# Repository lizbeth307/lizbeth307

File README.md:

<div align="center">
  
</div>

<div align="center">

</div>

<div align="center">

</div>

<div align="center">
  
</div>

<br>

<div align="center">

</div>

<br>

<div align="center">
  
</div>

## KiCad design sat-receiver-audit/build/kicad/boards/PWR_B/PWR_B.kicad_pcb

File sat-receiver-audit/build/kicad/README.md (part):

# KiCad SR-RX-v2.1 — відтворення схем і перевірок

> **Стан 20.10.2026:** ПЗ керування Pico/IMU та labd/labctl реалізоване й пройшло хостові тести; див. [актуальний запуск](../../software/README.md). Фізичне встановлення/приймання не виконано. Старі фрази про відсутню прошивку нижче описують етап 19.10.

> **Ревізія 23.10.2026:** CI workflow «SR-RX verification» (job `cad`) запускає `tools/run_checks.py --export` в офіційному образі `kicad/kicad:10.0.7` і порівнює результат із закоміченим. Допускаються лише рядки з датами експорту, абсолютними шляхами, build string KiCad, `"design_file"` і змінені рядки `"sha256"`/`"netlist_sha256"` у JSON-звітах (будь-який 64-символьний hash, не лише netlist); інша різниця дає помилку й артефакт `cad-regenerated` із патчем. `sr-rx-v2.pdf` побайтово не порівнюється: його фіксує лише `verification/pdf-export.json`, де змінений рядок `"sha256"` теж допускається. У цій ревізії R512 отримав `R_1210_3225Metric` (0.5 W); дубльовані підтяжки R102/R503/R507/R511 вилучено з графів під час злиття з гілкою `ccr-1537979d-cj7q9t` (а не позначено DNP): 750 елементів / 2181 підключений контакт / 466 мереж, 14 електричних сторінок. Зведення — [HANDOFF](../../HANDOFF.md#ревізія-23102026-claude-перевірка-виправлення-ci-план).

> **Ревізія генератора 24.10.2026:** E1 знову вміщується на одну сторінку; разом із п'ятою сторінкою E2 (блокувальні пари ±30 V, рішення власника v2.1) комплект має 14 електричних сторінок і зміст (PDF — 15 сторінок). Якщо остання сторінка аркуша була б майже порожньою (блоки займають менше 20 % площі), генератор переносить примітки ширшими рядками, наскільки дозволяє ширина креслення групи, і лишає найвужчий варіант, що заощаджує сторінку (для E1 — до 180 символів замість 110; примітка вужчої групи лишається вужчою: E1-02 — 121, E1-06 — 110). Рядок, де мітці знадобилося резервне (fallback) місце або дроти перетнули іншу мережу, розкладається ще раз із вільним кроком сітки біля кожного контакту шини між двома коробками, що стоять одна навпроти одної; цей варіант лишається, лише якщо в ньому менше fallback-міток або, за тієї самої їх кількості, щонайбільше вдвічі менше перетинів. Так розкладено HDMI J520–U520, PCIe J530–U530 та I²C/RESET між U302 і U303 (без перетинів) і SPI U309–U314 (частина перетинів лишилася): fallback-міток 0 замість 4; перетинів дротів без з'єднання на весь комплект — 45 (`drawing.wire_crossings`). Правий край вмісту разом із прив'язкою рядків до сітки лишається щонайменше на крок сітки (2.54 мм) від внутрішньої рамки. `generation-manifest.json` записує для кожної сторінки заповнення (`fill`), межу ширини приміток аркуша (`note_wrap_cap`), фактичну ширину рядків кожної примітки в символах (`note_wrap_chars`), fallback-мітки та перетини (`wire_crossings`), а також `sparse_last_pages`; `run_checks.py` відмовляє, якщо лишилася майже порожня остання сторінка або fallback-мітка. Згенеровані файли перегенеровує CI (`cad-regenerated`); оскільки з `netlist.xml` зник аркуш `/E1_02/`, змінився і вхід DC_CORE; DC_CORE перезаморожено 24.10.2026 (`refreeze_pcb`, вхід `14a5d398…`). Поле `electrical_sheets` у `verification/validation.json` тепер рахує лише аркуші з елементами (`schematic_sheets` — усі, `index_sheets` — кореневий зміст).

Поточна редакція від 19.10.2026 генерується локальними Python-інструментами з `design/E1.json`–`E5.json`. У вихідному коміті Claude `4653188` (у переписаній історії `ccr-1537979d-cj7q9t` — `4ffcc1d`) усі п'ять електричних E1–E5 були порожніми, а пізніші часткові аркуші Claude `e95fec4` (там — `9063cfa`) влито merge-комітом без зміни дерева; тому історичний опис «побудовано через KiCad MCP» нижче не підтверджує походження поточних схем.

## Склад актуального комплекту

- `sr-rx-v2.kicad_pro` / `sr-rx-v2.kicad_sch` — проєкт і кореневий зміст. E1–E5 поділяються генератором на додаткові електричні сторінки; їхній точний перелік — `generation-manifest.json`.

Креслення (з 23.10.2026). Кожна функціональна група — окремий блок на одній сторінці: заголовок один раз, примітки OPEN/TBD поруч із її частинами. У рядку сигнал іде зліва направо: мікросхеми, модулі, транзистори й послідовні елементи стоять на сигнальній лінії, підтягувальні резистори й контрольні точки — над нею, шунтові елементи (розв'язувальні конденсатори, дільники, TVS, демпфери) — під нею, земля — символ GND унизу. Контакти однієї мережі в рядку з'єднано ортогональними дротами з точками на T-з'єднаннях; контакт, до якого дріт довелося б вести довгим обхідним шляхом, отримує мітку. Кожне дерево дротів має рівно одну глобальну мітку з канонічною назвою мережі (рамка-стрілка — мережа виходить за межі групи, пряма рамка — мережа лише цієї групи), бо локальну мітку KiCad перейменував би на «/<аркуш>/<назва>» і змінив би netlist. Транзистори й діоди мають стандартні графічні символи KiCad (Device: Q_NMOS/Q_PMOS, D, D_Zener, D_Schottky, LED) з незмінною нумерацією контактів. Генератор сам відновлює зв'язність кожної сторінки з геометрії (кінці дротів, контакти, мітки, GND) і не записує сторінку, де вона розходиться з графом.
- `sr_rx_v2_completed.kicad_sym` — бібліотека з поточних графів; початкові `sr_rx_v2_pwr.kicad_sym` / `sr_rx_v2_sig.kicad_sym` збережені. Бібліотечні шляхи відносні.
- `sr-rx-v2.pdf` та `svg/` — результати CLI-експорту після успішних перевірок; не результат вимірювання заліза.
- `../../verification/erc.json` — повний сирий ERC; `validation.json` — незалежне зіставлення netlist із графами; інваріанти й розрахунок DC-detector — окремі відтворювані перевірки.

Розширені позначення нових детекторів E4 використовують R/C4400–4499; старі діапазони 100–599 збережені для початкових вузлів. Бібліотека відображає фізичні контакти IC і явно названі функціональні інтерфейси готових модулів; останні не є вигаданою нумерацією pad невідомої плати.

## Команди

З каталогу `sat-receiver-audit`, у Python 3 з установленим KiCad 10 CLI. Для офлайн-HTML додатково потрібні Pandoc і Python-залежності з `tools/requirements.txt` (`python3 -m pip install -r tools/requirements.txt`):

```bash
python3 tools/run_checks.py --export
python3 tools/build_bundle.py
```

Другу команду виконувати після успішного завершення першої. Якщо CLI не в PATH:

```bash
python3 tools/run_checks.py --kicad-cli /повний/шлях/до/kicad-cli --export
```

`run_checks.py` послідовно генерує схеми, експортує XML netlist, записує ERC, порівнює мережі, перевіряє незалежні електричні інваріанти та DC-detector, формує документи й за `--export` PDF/SVG. `build_bundle.py` пакує офлайн-HTML із вихідним архівом. Пакування не замінює перевірки. Запуск у CI після W2 GR-3 (sr-rx-verify, 07.11.2026; роз'єми джгутів — позиції графа) завершено: 839 елементів, 2555 контактів, 486 мереж, 163 явних NC, 17 сторінок разом зі змістом (16 електричних); ERC 0 помилок і 0 попереджень, netlist PASS (CI/model, не апаратний результат); повторний запуск дає байт-у-байт ті самі файли. Після будь-якої зміни графів ці результати потрібно отримати повторно.

PDF експортується без property popups та hierarchical links: у використаному KiCad 10.0.7 початковий експорт з анотаціями повертав exit 0, але неповний PDF. Генератор додатково перевіряє завершення `%%EOF`. Поточний PDF має 15 сторінок A2 (14 електричних і зміст; 24.10.2026 E1_02 злито в E1 і додано E2_05); його прив'язує до схем `verification/pdf-export.json`. Перевірку PDF-парсерами й візуальний перегляд виконано 23.10.2026 для PDF гілки `ccr-1537979d-cj7q9t` до злиття ([звіт](../../verification/pdf-visual-review.md)); на перегенерований після злиття PDF їхній результат не переноситься, доки сторінки не переглянуто знову.

## Межа готовності

**Апаратний випуск BLOCKED.** ERC та збіг netlist не перевіряють фізичну ревізію модулів, нагрівання, струм запуску, USB/PCIe SI, RF, калібровку батарейного ADC або механіку. [OPEN_ITEMS](../../OPEN_ITEMS.md) і [v2.1](../12-revision-v2.1.md) мають бути прочитані до монтажу. ISDT/raw-balance та щомісячне балансування заблоковані до E1-02; J102 DNP/service-only.

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
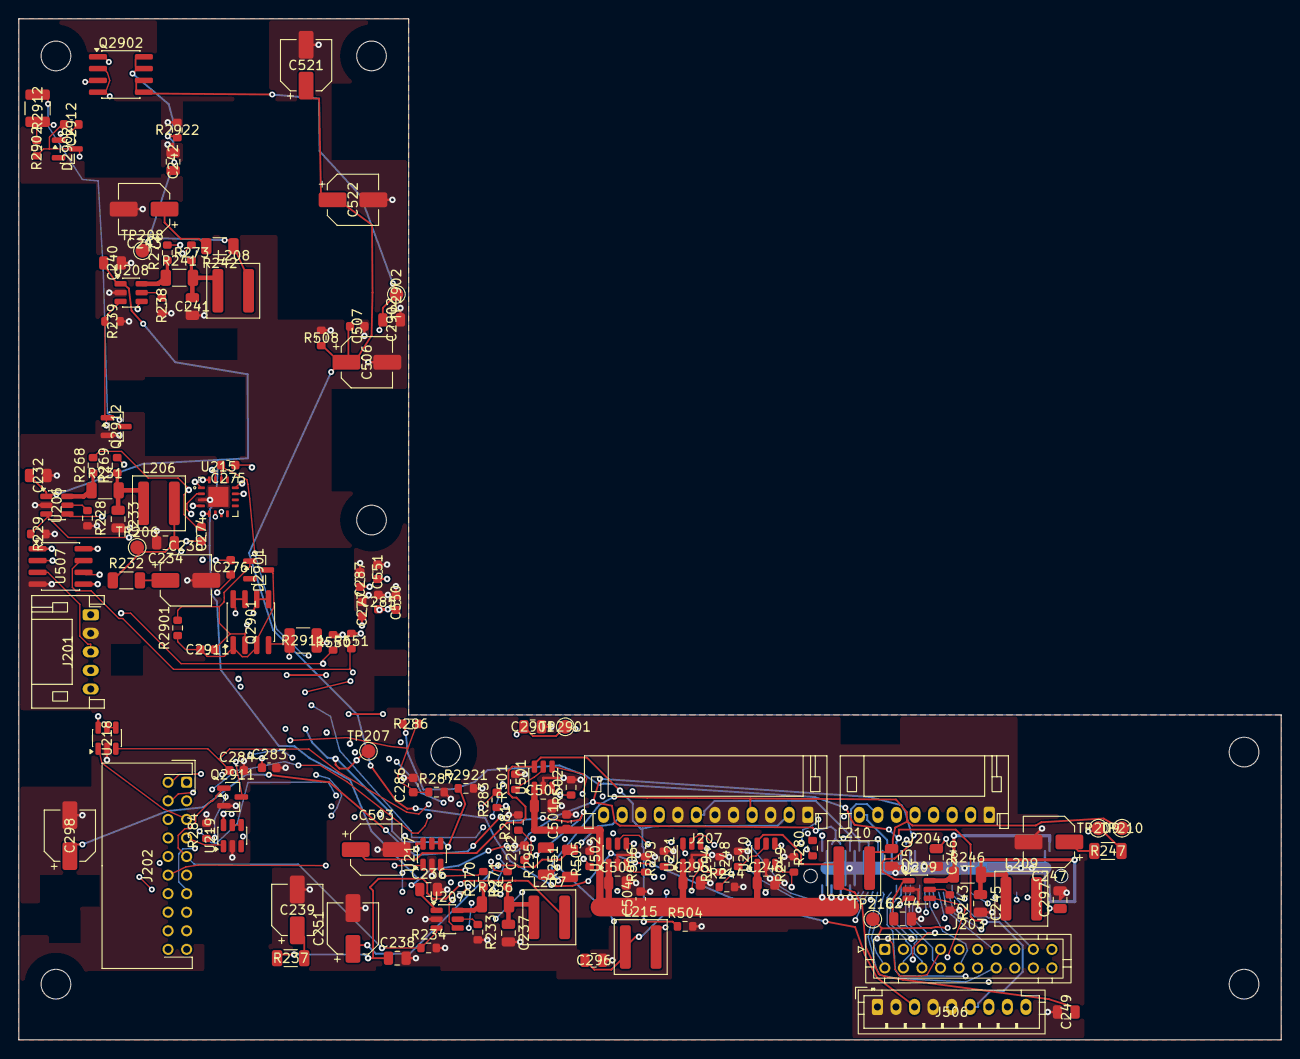
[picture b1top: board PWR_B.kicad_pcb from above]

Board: 6 copper layers, 136.0 x 110.0 mm, 144 parts (1 on the bottom side), 106 nets.

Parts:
C232, C233, C234, C236, C237, C238, C240, C241, C242, C244, C245, C246, C248, C249, C250, C295, C296, C297, C2901, C2902: 1uF 50V X7R C2012X7R1H105K125AB; C_0805_2012Metric
C235, C239, C243, C247, C251, C298, C506, C521, C522: 47uF 10V 16SVPG47M; CP_Elec_5x4.5
C274, C275, C276, C277, C283, C285, C287, C2911, C2912: 100nF 50V X7R C1608X7R1H104K080AA; C_0603_1608Metric
C282, C284, C286: 10nF 50V C0G C1608C0G1H103J080AA; C_0603_1608Metric
C501, C504, C507, C550, C551: 100nF X7R 10V; C_0603_1608Metric
C502, C505: 4.7uF X7R 10V; C_0805_2012Metric
C503: 47uF 10V; CP_Elec_5x4.5
D2901, D2902: BZX84C10-7-F; SOT-23
H1, H2, H3, H4, H5, H6, H7: NPTH_3.2mm
J201: X02S0-PWR: JST PH 5, боковий вхід, S02; JST_PH_S5B-PH-K_1x05_P2.00mm_Horizontal
J202: S02-PWR-SIG-1: JST PHD 2×10, боковий вхід, S02; JST_PHD_S20B-PHDSS_2x10_P2.00mm_Horizontal
J203: S02-PWR-SIG-2: JST PHD 2×10, верхній вхід, S02B; JST_PHD_B20B-PHDSS_2x10_P2.00mm_Vertical
J204: X04S1-PWR: JST PH 8, боковий вхід, S04; JST_PH_S8B-PH-K_1x08_P2.00mm_Horizontal
J207: SL2-PWR-PH: JST PH 12, боковий вхід, S20, S21, S2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; JST_PH_S12B-PH-K_1x12_P2.00mm_Horizontal
J209: B2B-PWRB: Samtec LSHM-150 2×50, PWR-B низ, стик 5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; Samtec_LSHM-150-xx.x-x-DV-N_2x50_P0.50mm_Vertical
J506: SL3-PWR-PH: JST PH 9, верхній вхід, S23, S34; JST_PH_B9B-PH-K_1x09_P2.00mm_Vertical
L206, L207, L208, L209, L210, L215: 1uH XAL5030-102MEC; L_Coilcraft_XAL5030-XXX
Q2901, Q2902: DMP6050SSD-13; SOIC-8_3.9x4.9mm_P1.27mm
Q2911, Q2912: 2N7002; SOT-23
R228, R233, R238: 88.7k 1%; R_0603_1608Metric
R229, R234, R239, R244, R249, R294: 100k 1%; R_0603_1608Metric
R231, R236, R241, R246: 0.200R 0.1% 0.25W Kelvin; R_1206_3216Metric
R232, R237, R242, R247, R251, R295: 0.15R 1% 0.25W; R_1206_3216Metric
R243, R293: 162k 1%; R_0603_1608Metric
R248: RILIM TBD (start 56.2k 1%); R_0603_1608Metric
R268, R269, R270, R271, R272, R273: 10.0R 1%; R_0603_1608Metric
R280: 85.6k 0.1%; R_0603_1608Metric
R281, R284, R287: 10.0k 0.1%; R_0603_1608Metric
R283: 90.9k 0.1%; R_0603_1608Metric
R286: 73.2k 0.1%; R_0603_1608Metric
R501: RILIM TBD (start 43.2k 1%); R_0603_1608Metric
R502, R506: 100k; R_0603_1608Metric
R504, R508: 10k; R_0603_1608Metric
R505: 34.8k 1%; R_0603_1608Metric
R550, R551, R2921, R2922: 4.7k 1%; R_0603_1608Metric
R2901, R2902: 220k 1%; R_0603_1608Metric
R2911, R2912: 4.7k 1% ≥0.25W; R_1210_3225Metric
TP206: BIAS_CH1; TestPoint_Pad_D1.5mm
TP207: BIAS_CH2; TestPoint_Pad_D1.5mm
TP208: BIAS_CH3; TestPoint_Pad_D1.5mm
TP209: BIAS_CH4; TestPoint_Pad_D1.5mm
TP210: VBUS_RTLB; TestPoint_Pad_D1.5mm
TP216: BIAS_SB_LNA; TestPoint_Pad_D1.5mm
TP2901: BIAS_CH2_PORT; TestPoint_Pad_D1.5mm
TP2902: BIAS_CH3_PORT; TestPoint_Pad_D1.5mm
U206, U207, U208, U209, U210, U221, U501, U502: TPS2553DBVR-1; SOT-23-6
U215: INA3221AIRGVR; TI_RGV0016A_VQFN-16-1EP_4x4mm_P0.65mm_EP2.16x2.16mm
U217, U218, U219: TLV3011BIDBVR; SOT-23-6
U507: TCA9517DR; SOIC-8_3.9x4.9mm_P1.27mm

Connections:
3V3_Q6A: C277.1, C283.1, C285.1, C287.1, C550.1, C551.1, J201.1, J204.2, J209.2, R550.2, R551.2, U215.4, U215.5, U215.16, U217.6, U218.6, U219.6, U507.1, U507.5, U507.8
AUX12: J209.34, J506.6, R286.1
BIAS_CH1: C234.1, J204.3, L206.2, R232.1, TP206.1
BIAS_CH1_DAMP: C235.1, R232.2
BIAS_CH2: C238.1, L207.2, Q2901.7, Q2901.8, R237.1, R2921.1, TP207.1
BIAS_CH2_DAMP: C239.1, R237.2
BIAS_CH2_PORT: C2901.1, J204.4, Q2901.5, Q2901.6, TP2901.1
BIAS_CH3: C242.1, L208.2, Q2902.7, Q2902.8, R242.1, R2922.1, TP208.1
BIAS_CH3_DAMP: C243.1, R242.2
BIAS_CH3_PORT: C2902.1, J204.5, Q2902.5, Q2902.6, TP2902.1
BIAS_CH4: C246.1, J204.6, L209.2, R247.1, TP209.1
BIAS_CH4_DAMP: C247.1, R247.2
BIAS_SB_LNA: C297.1, J207.11, L215.2, R295.1, TP216.1
BONI13V8: J209.26, R283.1
BONI13V8_PORT: J207.9, J209.38
CHG_INHIBIT: J202.1, J209.17
E1_BAT_ADC: J202.2, J209.19
E2_BLK2_G: C2911.2, D2901.1, Q2901.2, Q2901.4, R2901.2, R2911.1
E2_BLK2_S: C2911.1, D2901.3, Q2901.1, Q2901.3, R2901.1
E2_BLK2_SINK: Q2911.3, R2911.2
E2_BLK3_G: C2912.2, D2902.1, Q2902.2, Q2902.4, R2902.2, R2912.1
E2_BLK3_S: C2912.1, D2902.3, Q2902.1, Q2902.3, R2902.1
E2_BLK3_SINK: Q2912.3, R2912.2
E2_LNA1_SHUNT: C233.1, L206.1, R231.2, R269.1
E2_LNA1_SW: R231.1, R268.1, U206.6
E2_LNA2_SHUNT: C237.1, L207.1, R236.2, R271.1
E2_LNA2_SW: R236.1, R270.1, U207.6
E2_LNA3_SHUNT: C241.1, L208.1, R241.2, R273.1
E2_LNA3_SW: R241.1, R272.1, U208.6
E2_LNA4_SHUNT: C245.1, J209.99, L209.1, R246.2
E2_LNA4_SW: J209.100, R246.1, U209.6
E2_RTLB_SW: C249.1, L210.1, U210.6
E2_SB_DAMP: C298.1, R295.2
E2_SB_ILIM: R293.1, U221.5
E2_SB_SW: C296.1, L215.1, U221.6
E2_U206_ILIM: R228.1, U206.5
E2_U207_ILIM: R233.1, U207.5
E2_U208_ILIM: R238.1, U208.5
E2_U209_ILIM: R243.1, U209.5
E2_U210_ILIM: R248.1, U210.5
E2_U215_IM1: C274.2, R269.2, U215.11
E2_U215_IM2: C275.2, R271.2, U215.14
E2_U215_IM3: C276.2, R273.2, U215.1
E2_U215_IP1: C274.1, R268.2, U215.12
E2_U215_IP2: C275.1, R270.2, U215.15
E2_U215_IP3: C276.1, R272.2, U215.2
E2_U217_REF: U217.4, U217.5
E2_U217_SENSE: C282.1, R280.2, R281.1, U217.3
E2_U218_REF: U218.4, U218.5
E2_U218_SENSE: C284.1, R283.2, R284.1, U218.3
E2_U219_REF: U219.4, U219.5
E2_U219_SENSE: C286.1, R286.2, R287.1, U219.3
E5_U501_ILIM: R501.1, U501.5
E5_U502_ILIM: R505.1, U502.5
EN_AUX12: J202.3, J209.21
EN_BONI: J202.4, J209.23
EN_HFP: J203.2, J209.27
EN_LABPORT: J202.6, R506.1, U502.3
EN_LIME3V3: J203.14, J209.25
EN_LNA1: J202.8, R229.1, U206.3
EN_LNA2: J202.9, Q2911.1, R234.1, U207.3
EN_LNA3: J202.10, Q2912.1, R239.1, U208.3
EN_LNA4: J202.11, R244.1, U209.3
EN_LNB: J203.15, J209.85
EN_RTLA: J202.13, R502.1, U501.3
EN_RTLB: J202.14, R249.1, U210.3
EN_SB_LNA: J202.15, R294.1, U221.3
FAULT_HFP: J203.18, J209.31
FAULT_LABPORT: J202.17, U502.4
FAULT_LNA1: J202.18, U206.4
FAULT_LNA2: J202.19, U207.4
FAULT_LNA3: J202.20, U208.4
FAULT_LNA4: J203.1, U209.4
FAULT_RTLA: J202.16, U501.4
FAULT_RTLB: J203.3, U210.4
FLT_BONI: J203.4, J209.33
FLT_LIME3V3: J203.5, J209.35
FLT_LNB: J203.6, J209.37
FLT_SB_LNA: J203.7, U221.4
GND: C232.2, C233.2, C234.2, C235.2, C236.2, C237.2, C238.2, C239.2, C240.2, C241.2, C242.2, C243.2, C244.2, C245.2, C246.2, C247.2, C248.2, C249.2, C250.2, C251.2, C277.2, C282.2, C283.2, C284.2, C285.2, C286.2, C287.2, C295.2, C296.2, C297.2, C298.2, C501.2, C502.2, C503.2, C504.2, C505.2, C506.2, C507.2, C521.2, C522.2, C550.2, C551.2, C2901.2, C2902.2, J201.2, J204.1, J207.1, J207.3, J207.5, J207.6, J207.8, J207.10, J209.3, J209.4, J209.7, J209.8, J209.11, J209.12, J209.15, J209.16, J209.20, J209.24, J209.28, J209.32, J209.36, J209.40, J209.42, J209.97, J209.98, J506.1, J506.2, J506.4, J506.5, Q2911.2, Q2912.2, R228.2, R229.2, R233.2, R234.2, R238.2, R239.2, R243.2, R244.2, R248.2, R249.2, R281.2, R284.2, R287.2, R293.2, R294.2, R501.2, R502.2, R504.2, R505.2, R506.2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
I2C0_SCL: J203.8, J209.39
I2C0_SDA: J203.9, J209.65
I2C2_SCL: J201.4, J209.43, U215.6, U507.2
I2C2_SDA: J201.3, J209.45, U215.7, U507.3
I2CB_SCL: J506.7, R551.1, U507.7
I2CB_SDA: J506.8, R550.1, U507.6
IMU_RX: J203.10, J209.47
IMU_TX: J203.11, J209.49
INA228_ALERT: J203.12, J209.51
LAB5: C248.1, C295.1, C501.1, C502.1, C504.1, C505.1, J209.1, J209.5, J209.9, J209.13, U210.1, U221.1, U501.1, U502.1
LAB5_RLY: J204.7, J209.18, J209.22
LNA4V5: C232.1, C236.1, C240.1, C244.1, J209.6, J209.10, U206.1, U207.1, U208.1, U209.1
LNB13V2: J204.8, J209.30, R280.1
OVP_LNB_N: J203.13, J209.53
PG_BONI: J202.5, U218.1
PG_LNB: J202.12, U217.1
PICO_DISP_EN: J203.16, J209.55
PICO_OFF: J203.17, J209.57
PTC_AUX: J202.7, U219.1
PWR_BUTTON: J203.19, J209.59
SLED_DET: J203.20, J506.9
VBUS_HFP: J207.7, J209.14
VBUS_LABPORT: C506.1, C507.1, C521.1, C522.1, J506.3, R508.1, U502.6
VBUS_RTLA: C503.1, J207.2, R504.1, U501.6
VBUS_RTLB: C250.1, J207.4, L210.2, R251.1, TP210.1
VBUS_RTLB_DAMP: C251.1, R251.2

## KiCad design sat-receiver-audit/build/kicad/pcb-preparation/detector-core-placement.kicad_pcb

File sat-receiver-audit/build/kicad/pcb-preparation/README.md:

# Unrouted DC detector core placement

**NOT FOR FABRICATION. No Gerbers.** The `.kicad_pcb` is a concrete 71-component KiCad 10 placement starter using real portable footprint candidates, with every source physical pin assigned to its original net. It has no tracks, vias or zones. The 125 × 115 mm outline and two-layer configuration are engineering candidates; enclosure fit, mounting and stackup remain unapproved.

Open `detector-core-placement.kicad_pcb` in KiCad; the adjacent project and relative `fp-lib-table` resolve the bundled resources. `detector-core-placement.svg` and `.png` provide native board previews. The board silkscreen marks the unreleased status.

The native read-back audit and independent parser confirm 71 parts, 187 pads, 180 connected pads, seven NC pads and 40 nets. The eight external boundary nets have no invented connector pads. Eighteen RF-port tap/bleed components are excluded, so no RF transmission-line routing is present. Fifty passive footprints remain unqualified placement proposals.

`drc-raw.json` is the full unfiltered KiCad result: **140 unconnected errors, zero other/geometric violations, zero ignored checks; DRC exit 5**. The five normally ignored check categories are explicitly enabled as warning in the project. There is no production DRC pass. Full-project schematic parity was not requested for this subset board; exact source-node → subset-pad correspondence is audited separately.

- `placement-audit.json`: every source pin, board pad, net, position and resource hash.
- `footprint-provenance.json`: official KiCad 10.0.7 R0402 package/resource hash and license reference.
- `drc-command.log`, `svg-command.log`: native command output.
- `../../../verification/pcb-review.md` and `.json`: review details and release gates (paths relative to this folder).

From the repository root, with KiCad Python and CLI installed:

```sh
python3 pcb/generate_layout.py
python3 pcb/generate_layout.py --check
```

In the current container, the official Ubuntu KiCad 10.0.7 package and its runtime dependencies were extracted locally. Use:

```sh
python3 pcb/generate_layout.py --runtime-root /tmp/kicad-runtime/root --kicad-cli /tmp/kicad-runtime/kicad-cli
python3 pcb/generate_layout.py --runtime-root /tmp/kicad-runtime/root --check
```

The runtime-root option sets `LD_LIBRARY_PATH` and `PYTHONPATH` before importing native `pcbnew`; this is optional on an installed KiCad system. The script validates real footprint pin sets, generates and native-parses the board, performs an exact source-to-pad audit, invokes raw DRC with all severities, and exports the native SVG. PyMuPDF optionally renders the PNG. Generated output is atomically published. The read-only `--check` verifies source/board/resource snapshot consistency; it does not assert production readiness.

Regenerating changes native UUIDs; repeat the consistency audit after changes and update snapshot review hashes before any release claim. Run `python3 pcb/prepare.py` and its `--check` before generation when source metadata changes.

The independent checker uses only the Python standard library and reads the source input, board and raw DRC directly, without importing generator code or requiring native KiCad:

```sh
python3 verification/independent_pcb_check.py
```

It exits nonzero on mismatched components/pads/nets, invalid NCs/footprint IDs, duplicate UUIDs, unexpected routing, invalid outline, excluded RF-port components or incomplete raw DRC coverage.

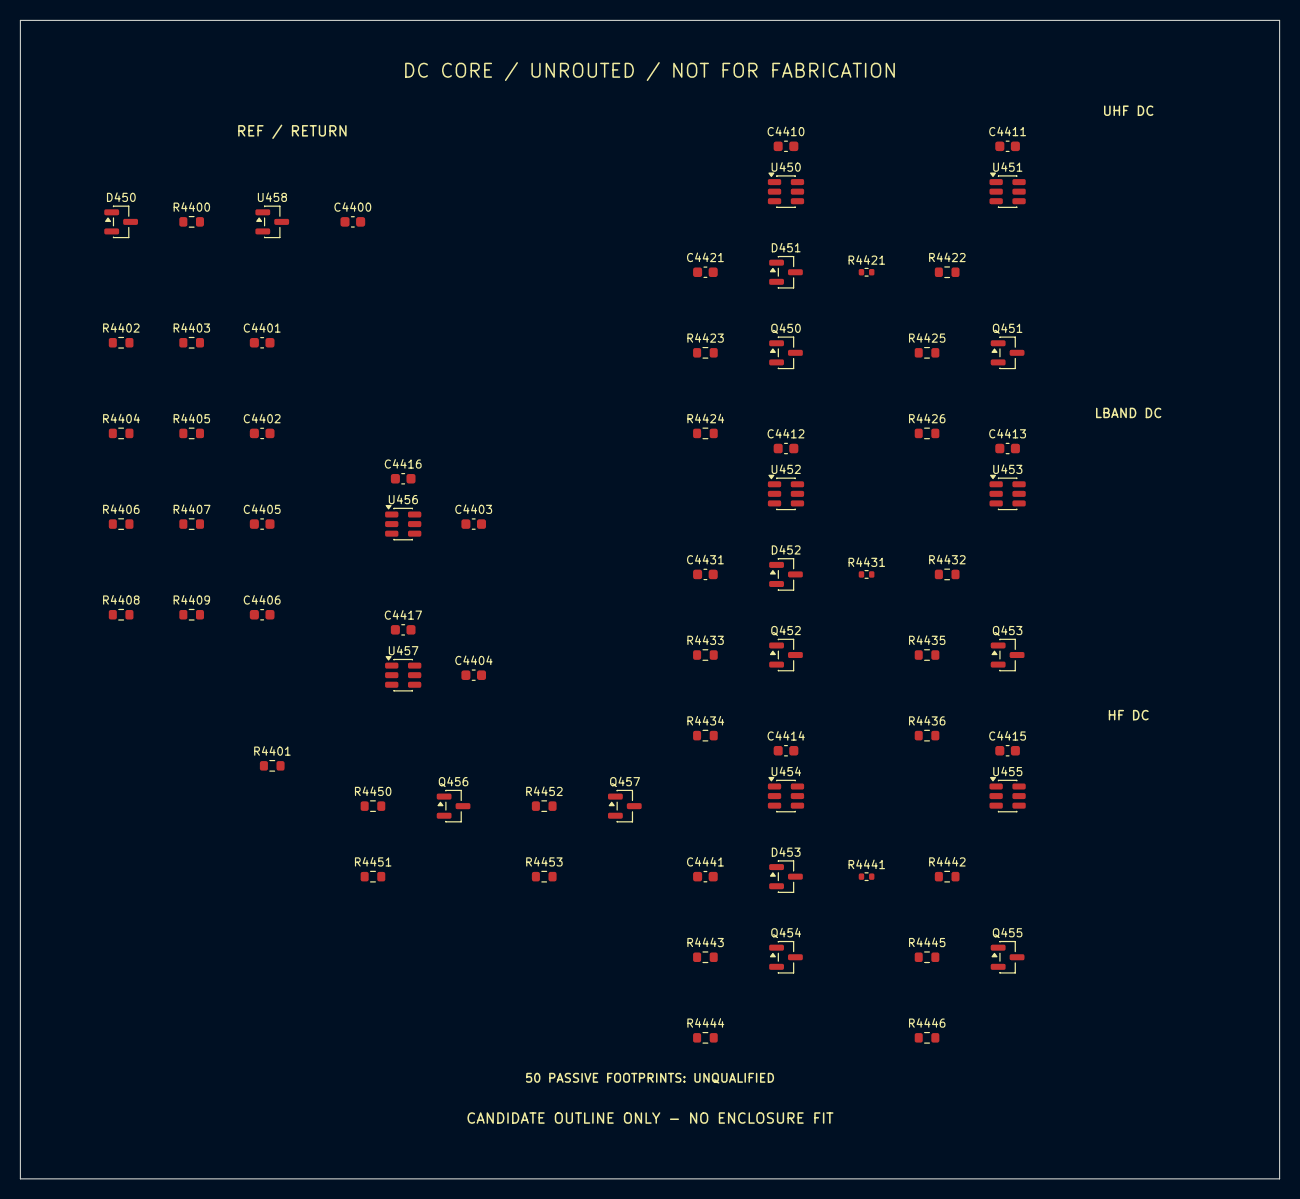
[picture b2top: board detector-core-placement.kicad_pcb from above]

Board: 2 copper layers, 125.0 x 115.0 mm, 71 parts (0 on the bottom side), 34 nets, no tracks yet.

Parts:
C4400: 100 nF X7R 10 V; C_0603_1608Metric
C4401, C4402, C4405, C4406, C4421, C4431, C4441: 10 nF C0G 50 V; C_0603_1608Metric
C4403, C4404: 1 nF C0G 50 V; C_0603_1608Metric
C4410, C4411, C4412, C4413, C4414, C4415, C4416, C4417: 100 nF X7R 10 V local decoupling; C_0603_1608Metric
D450: BAV199 reference reverse-feed isolation; SOT-23
D451, D452, D453: BAV199 sense clamps; SOT-23
Q450, Q451, Q452, Q453, Q454, Q455, Q456, Q457: AO3400A; SOT-23
R4400: 150 Ω 1% 0.125 W; R_0603_1608Metric
R4401: 10 kΩ 1% Q6A off-state bleed; R_0603_1608Metric
R4402, R4405: 26.7 kΩ 0.1%; R_0603_1608Metric
R4403, R4404: 25.5 kΩ 0.1%; R_0603_1608Metric
R4406: 10.0 kΩ 0.1%; R_0603_1608Metric
R4407, R4408: 24.9 kΩ 0.1%; R_0603_1608Metric
R4409: 33.2 kΩ 0.1%; R_0603_1608Metric
R4421, R4431, R4441: 23.2 kΩ 0.1% 0402; R_0402_1005Metric
R4422, R4432, R4442: 49.9 kΩ 0.1%; R_0603_1608Metric
R4423, R4425, R4433, R4435, R4443, R4445, R4450, R4452: 100 Ω; R_0603_1608Metric
R4424, R4426, R4434, R4436, R4444, R4446, R4451, R4453: 100 kΩ; R_0603_1608Metric
U450, U451, U452, U453, U454, U455, U456, U457: TLV3012BIDBVR; SOT-23-6
U458: LM4040A20IDBZR 2.048 V 0.1% shunt; SOT-23

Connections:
3V3_Q6A: C4410.1, C4411.1, C4412.1, C4413.1, C4414.1, C4415.1, C4416.1, C4417.1, D450.1 (A1), R4401.1, U450.6 (V+), U451.6 (V+), U452.6 (V+), U453.6 (V+), U454.6 (V+), U455.6 (V+), U456.6 (V+), U457.6 (V+)
E4_DCS_HF_HIGH_GATE: Q455.1 (G), R4445.2, R4446.1
E4_DCS_HF_HIGH_OK: R4445.1, U455.1 (OUT)
E4_DCS_HF_LOW_GATE: Q454.1 (G), R4443.2, R4444.1
E4_DCS_HF_LOW_OK: R4443.1, U454.1 (OUT)
E4_DCS_HF_SENSE: C4441.1, D453.3 (K1_A2), R4441.2, R4442.2, U454.3 (IN+), U455.4 (IN-)
E4_DCS_HF_SINK_MID: Q454.2 (S), Q455.3 (D)
E4_DCS_HIGH: C4402.1, R4404.2, R4405.1, U451.3 (IN+), U453.3 (IN+), U455.3 (IN+)
E4_DCS_LBAND_HIGH_GATE: Q453.1 (G), R4435.2, R4436.1
E4_DCS_LBAND_HIGH_OK: R4435.1, U453.1 (OUT)
E4_DCS_LBAND_LOW_GATE: Q452.1 (G), R4433.2, R4434.1
E4_DCS_LBAND_LOW_OK: R4433.1, U452.1 (OUT)
E4_DCS_LBAND_SENSE: C4431.1, D452.3 (K1_A2), R4431.2, R4432.2, U452.3 (IN+), U453.4 (IN-)
E4_DCS_LBAND_SINK_MID: Q452.2 (S), Q453.3 (D)
E4_DCS_LOW: C4401.1, R4402.2, R4403.1, U450.4 (IN-), U452.4 (IN-), U454.4 (IN-)
E4_DCS_REF: C4400.1, D451.2 (K2), D452.2 (K2), D453.2 (K2), R4400.2, R4402.1, R4404.1, R4406.1, R4408.1, R4422.1, R4432.1, R4442.1, U458.1 (CATHODE)
E4_DCS_REF12_HIGH: C4404.1, U457.3 (IN+), U457.5 (REF)
E4_DCS_REF12_LOW: C4403.1, U456.4 (IN-), U456.5 (REF)
E4_DCS_REF_FEED: D450.3 (K1_A2), R4400.1
E4_DCS_REF_GATE_HIGH: Q457.1 (G), R4452.2, R4453.1
E4_DCS_REF_GATE_LOW: Q456.1 (G), R4450.2, R4451.1
E4_DCS_REF_GOOD_HIGH: R4452.1, U457.1 (OUT)
E4_DCS_REF_GOOD_LOW: R4450.1, U456.1 (OUT)
E4_DCS_REF_PG_HIGH: C4406.1, R4408.2, R4409.1, U457.4 (IN-)
E4_DCS_REF_PG_LOW: C4405.1, R4406.2, R4407.1, U456.3 (IN+)
E4_DCS_REF_RETURN_MID: Q456.2 (S), Q457.3 (D)
E4_DCS_RETURN: Q451.2 (S), Q453.2 (S), Q455.2 (S), Q456.3 (D)
E4_DCS_UHF_HIGH_GATE: Q451.1 (G), R4425.2, R4426.1
E4_DCS_UHF_HIGH_OK: R4425.1, U451.1 (OUT)
E4_DCS_UHF_LOW_GATE: Q450.1 (G), R4423.2, R4424.1
E4_DCS_UHF_LOW_OK: R4423.1, U450.1 (OUT)
E4_DCS_UHF_SENSE: C4421.1, D451.3 (K1_A2), R4421.2, R4422.2, U450.3 (IN+), U451.4 (IN-)
E4_DCS_UHF_SINK_MID: Q450.2 (S), Q451.3 (D)
GND: C4400.2, C4401.2, C4402.2, C4403.2, C4404.2, C4405.2, C4406.2, C4410.2, C4411.2, C4412.2, C4413.2, C4414.2, C4415.2, C4416.2, C4417.2, C4421.2, C4431.2, C4441.2, D451.1 (A1), D452.1 (A1), D453.1 (A1), Q457.2 (S), R4401.2, R4403.2, R4405.2, R4407.2, R4409.2, R4424.2, R4426.2, R4434.2, R4436.2, R4444.2, R4446.2, R4451.2, R4453.2, U450.2 (V-), U451.2 (V-), U452.2 (V-), U453.2 (V-), U454.2 (V-), U455.2 (V-), U456.2 (V-), U457.2 (V-), U458.2 (ANODE), U458.3 (STAR_CONNECT_ANODE)

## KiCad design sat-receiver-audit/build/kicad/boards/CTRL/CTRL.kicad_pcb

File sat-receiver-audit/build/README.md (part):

<!-- SR-RX-v2.1 notice 2026-10-19: STACK.md remains the source of truth -->
> **Джерело істини — [STACK.md](../STACK.md) (стек v2).** Поправки v2.1 від 19.10.2026 зафіксовано в STACK; подробиці — у [поправках v2.1](../build/12-revision-v2.1.md). Стан — [COMPLETION](../COMPLETION.md), ворота приймання — [OPEN_ITEMS](../OPEN_ITEMS.md), монтажні карти — [E5](../design/E5-connection-guide.md). Нижче — матеріал пакета v2; якщо він розходиться зі STACK.md, правильний STACK.md.
>
> **Апаратний випуск BLOCKED:** пристрій не зібрано й не випробувано. Щомісячна зарядка/балансування через ISDT 608PD та зовнішній raw-balance порт **заборонені до закриття E1-02**; J102 — DNP/service-only. Внутрішні sense-проводи Daly зберігаються. Вимкнення головного ключа або запобіжник не доводять ізоляцію B0/P−; не переносити B0 на P− і не застосовувати raw B− як обхід.
>
> **Старі габарити, маса й ціни не є чинною специфікацією закупівлі.** LAB5 змінено на D36V50F5 #4091 (25.4×25.4×9.5 mm); S-band LaNA WB + sysmocom cf2235-kt30 перенесено в зовнішній антенний вузол, а не всередину ручного корпуса. Деталі та фільтр 2170–2300 MHz — у поправках v2.1. Кошторис v2 залишається історичною оцінкою, новий перелік схеми — [11-schematic-bom.csv](../build/11-schematic-bom.csv).
>
> Власні labd/labrx, Pico/IMU/HMI і експериментальні бібліотечні патчі реалізовані як вихідний код і перевірені на хості та в ARM64 VM (ПЗ 0.3.1; [software/README](../software/README.md), [14-control-software](14-control-software.md)), але не встановлені, не прошиті й не кваліфіковані на Q6A/MCU; кваліфікованої NPU/HTP-системи немає. `readiness-contract.json` — специфікація, не працюючий GPIO-захист. Остаточні звіти й експорти формуються після фінального запуску `tools/run_checks.py --export`; точні лічильники та висновок ERC беріть із згенерованих звітів, а не з історичного тексту.
>
> Файли v2.1 цього каталогу: [11-schematic-bom](11-schematic-bom.md), [12-revision-v2.1](12-revision-v2.1.md), [13-pcb-preparation](13-pcb-preparation.md), [14-control-software](14-control-software.md), [15-rishennia-komplektu](15-rishennia-komplektu.md) (рішення для повного комплекту документації, 24.10–07.11.2026). Ревізія 23.10.2026 (виправлення findings, CI, R512 1210, R102/R503/R507/R511 вилучено, відсічка 13.05 V) — у [HANDOFF](../HANDOFF.md#ревізія-23102026-claude-перевірка-виправлення-ci-план).

---

# Пакет збирання — супутниковий приймач лише на прийом і портативна радіолабораторія

Версія: v2, 18.10.2026. Джерело істини — [../STACK.md](../STACK.md) (стек v2). Якщо файл пакета розходиться зі STACK.md, правильний STACK.md. Поправки v2.1 зафіксовано в STACK; подробиці — у [12-revision-v2.1.md](12-revision-v2.1.md).

**Статус:** теоретичний проєкт — перевірити на стенді. Деталі, рейки, піни й процедури звірено з повторним аудитом (P4), рішеннями щодо аналогів (P5) і багатьма перевірками. Але жодна збірка ще не вимірювалася. Усе, що позначено «модель», «TBD» або «не перевірено», треба виміряти на стенді (див. `09-testy.md`, STACK.md §8, §8.1, §8.2).

## Правила, які діють для всього пакета
- Лише прийом в ефірі. Генератори, VNA і шумове джерело підключаються тільки кондуктивно, у навантаження або DUT і ніколи в антену.
- Без декодування приватного змісту. Без трактів під військовий зв'язок.
- Без рамкових антен і H-field зондів, без тарілок. Антени — патч/чип або складані частини ≈20–23 см.
- Місце визначається з GNSS, таблиць міст немає.
- LimeSDR Micro M.2 входить у збірку за замовчуванням, його TX заблоковано.

## Файли

| Файл | Що це | Для чого |
|---|---|---|
| `01-blok-skhema.svg`, `01-blok-skhema.md` | Блок-схема пристрою й лабораторії | Загальна картина: блоки, шини, шляхи сигналу |
| `02-zhyvlennia.svg`, `02-zhyvlennia.md` | Схема живлення, таблиця рейок | Пак, BMS, рейки, обмеження струму, захист, порядок вмикання, час роботи |
| `03-rf-trakt.svg`, `03-rf-trakt.md` | РЧ-тракт | Кожен вхід → фільтр/LNA → інжектор → перемикач → SDR, правила bias/DC, таблиця цілей |
| `04-pidkliuchennia-pinout.md`, `04-header-40pin.svg` | Підключення і розпіновка | 40-pin, I2C, UART, розширювачі MCP23017 #1/#3/#4, USB і VBUS, роз'єми корпусу, кабелі |
| `05-roztashuvannia-front.svg`, `05-roztashuvannia-section.svg`, `05-roztashuvannia-panel.svg`, `05-mekhanika.md` | Розташування і механіка | Вигляд спереду, переріз шарів, стінки з усіма портами, розміри в мм, тепло, герметизація, маса |
| `06-anteny.md`, `06-anteny-komplekty.svg` | Антенні комплекти | Розміри в складеному і розкладеному вигляді, збирання, налаштування лише на прийом, пакування |
| `07-pz-vstanovlennia.md` | Встановлення ПЗ | Образ, утримане ядро, оверлеї, збірки драйверів і декодерів, алоу-листи, CI-перевірки відсутності TX і приватних шляхів |
| `08-zbyrannia.md` | Інструкція зі збирання | 18 кроків: деталі → дія → перевірка з порогом |
| `09-testy.md` | План тестів | Стендові ворота, приймання кожної деталі й аналога, самоперевірки правил, тести Lime за 30 днів, польові тести |
| `10-bom.csv`, `10-bom.md` | Склад (BOM) v2, історичний кошторис | 145 позицій з цінами USD / ЄС з ПДВ, статусом і умовами; підсумки за рівнями; порядок закупівлі |

**Файли етапу 3 (v2.1, 07.11.2026)** — за ними збирають; там, де вони розходяться з файлами v2 вище, правильні вони (і STACK.md):

| Файл | Що це | Для чого |
|---|---|---|
| `10-zakupivlia.md`, `10-zakupivlia.csv` | Закупівля з бази деталей | Кожна деталь графів з MPN, SKU, станом наявності на дату знімка або TBD з причиною; згенеровано `tools/build_parts.py` |
| `10-zakupivlia-kriplennia.csv`, `10-zakupivlia-inshe.csv`, `10-dzhgut-rodyny.csv` | Решта закупівлі | Кріплення, ущільнення, витратні матеріали й інструмент поза схемою (`assembly_items`); рядки v2 поза схемою; родини роз'ємів джгутів |
| `10-jlc-bom.csv` | BOM збирання плат JLC | Рядки за платами (PWR, RF, CTRL і малі плати) |
| `11-schematic-bom.md`, `11-schematic-bom.csv` | BOM схеми | Перелік графів E1–E5 (не кошик) |
| `12-revision-v2.1.md` | Поправки v2.1 | LAB5, S-band pod і інші зміни проти v2 |
| `13-pcb-preparation.md` | Підготовка PCB | Домени й фізичні плати, footprint і звірка з KiCad; Gerber ще немає (хвиля 2) |
| `14-control-software.md` | ПЗ керування | Стан labd/Pico/IMU і посилання на код |
| `15-rishennia-komplektu.md` | Рішення комплекту | Кожне технічне рішення пакета з причиною |
| `16-dzhgut.md` (+ `.csv`, `-rozyemy.csv`, `-pidsumok.csv`) | Джгути провід за проводом | Сегменти, роз'єми на платах, перерізи, кольори, маркери, кількість для закупівлі |
| `17-kriplennia.md` (+ `.csv`) | Кріплення й моменти | Кожне кріплення, момент з джерелом або TBD (купон) |
| `18-markuvannia.md` (+ `.csv`, `-arkush.svg`) | Маркування | Наклейки портів і попереджень, аркуш для друку |
| `19-zapusk-plat.md` (+ `.csv`) | Запуск плат | Стани живлення, контрольні точки, ступені обмеження струму стенда |
| `20-forma-stendu.md` (+ `.csv`) | Бланк стенда | Порожні поля для записів кожного рядка 09 і воріт |
| `21-poriadok-zbyrannia.md` | Порядок збирання | Кроки E0–E10 (з E9b — зовнішній S-band вузол), розбирання і сервіс |
| [`../mechanical/README.md`](../mechanical/README.md) | Механіка | Креслення 1:1: корпус M-01…M-13, плати B-, антени A-, S-band pod P-01/P-02, пак IMU I-01; STL і STEP; звіт посадки (MODEL FIT ONLY) |
| [`../design/parts/README.md`](../design/parts/README.md) | База деталей | Схема `parts.json`, знімки наявності, правила TBD |
| [`../deployment/image/README.md`](../deployment/image/README.md) | Образ ОС | Рецепт A/B UFS, комплект відновлення, наскрізний порядок до UFS (CI-модель, кандидат) |

## Порядок роботи

Чинний порядок v2.1 (етап 3). Відкриті рішення, закупівлі й ворота — [HANDOFF, ревізія 07.11.2026](../HANDOFF.md#ревізія-07112026-етап-3).

1. **Купити** за [`10-zakupivlia.md`](10-zakupivlia.md) (+ `10-zakupivlia-kriplennia.csv` і `10-zakupivlia-inshe.csv`); наявність і ціни — знімки на дату в файлі, перед замовленням перечитати. `10-bom.md` — лише історичний кошторис v2. Строки Lime (STACK.md §9.1 крок 10, §1.1 C1) діють і далі.
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
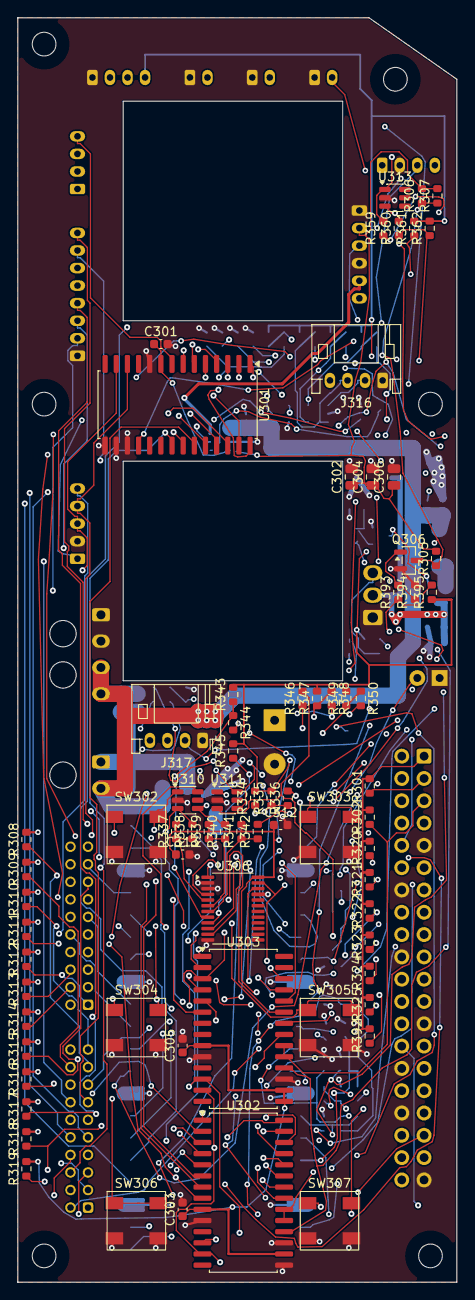
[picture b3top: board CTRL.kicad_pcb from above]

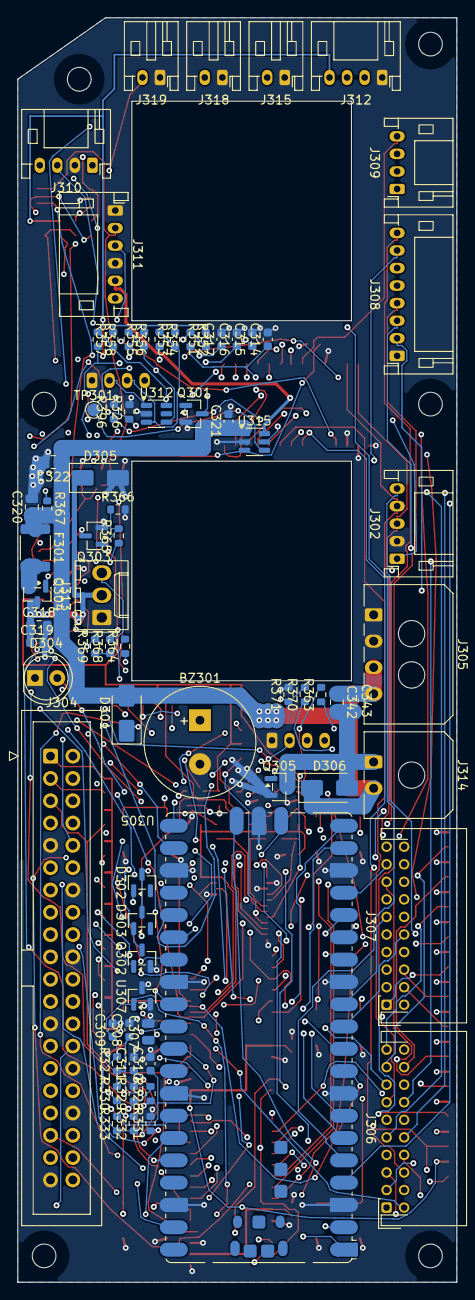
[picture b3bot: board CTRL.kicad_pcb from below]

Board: 4 copper layers, 50.0 x 144.0 mm, 153 parts (75 on the bottom side), 126 nets.

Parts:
BZ301: CPT-1207-3TH; Buzzer_SameSky_CPT-1207-3TH_D12.5mm_P5.0mm
C301, C303, C305, C308, C309, C310, C311, C312, C319, C321, C343: 100n 16V; C_0603_1608Metric
C302, C304, C306, C307, C318, C320, C342: 10u 10V; C_0805_2012Metric
C313: 1u 10V; C_0603_1608Metric
C314, C315, C316, C317: 10n 16V; C_0603_1608Metric
C322: 4.7u 10V; C_0805_2012Metric
D301: SS14; D_SMA
D302, D303: BAT54; SOT-23
D304: WP7113LSECK/J3 red; LED_D5.0mm_KA
D305, D306: SS14 flyback; D_SMA
F301: MF-MSMF075/24-2 0.75A; Fuse_1812_4532Metric
H1, H2, H3, H4, H5, H6: NPTH_2.7mm
J302: Power-board control harness DESIGN; JST_PH_S5B-PH-K_1x05_P2.00mm_Horizontal
J304: X01I1-CTRL: IDC 2×20, бокс, S01; IDC-Header_2x20_P2.54mm_Vertical
J305: X02P1-CTRL: Molex Micro-Fit 3.0 4, кутова, S02; Molex_Micro-Fit_3.0_43650-0400_1x04_P3.00mm_Horizontal
J306: S02-CTRL-SIG-1: JST PHD 2×10, боковий вхід, S02; JST_PHD_S20B-PHDSS_2x10_P2.00mm_Horizontal
J307: S02-CTRL-SIG-2: JST PHD 2×10, боковий вхід, S02; JST_PHD_S20B-PHDSS_2x10_P2.00mm_Horizontal
J308: X03S1-CTRL: JST PH 8, боковий вхід, S03; JST_PH_S8B-PH-K_1x08_P2.00mm_Horizontal
J309: X03S2-CTRL: JST PH 4, боковий вхід, S03; JST_PH_S4B-PH-K_1x04_P2.00mm_Horizontal
J310: S15-30-CTRL: JST PH 4, боковий вхід, S15, S30; JST_PH_S4B-PH-K_1x04_P2.00mm_Horizontal
J311: S24-25-CTRL: JST PH 6, боковий вхід, S24, S25; JST_PH_S6B-PH-K_1x06_P2.00mm_Horizontal
J312: X26S1-CTRL: JST PH 4, боковий вхід, S26; JST_PH_S4B-PH-K_1x04_P2.00mm_Horizontal
J313: X27F1-CTRL: Molex KK 254 3, верхній вхід, S27; Molex_KK-254_AE-6410-03A_1x03_P2.54mm_Vertical
J314: X28P1-CTRL: Molex Micro-Fit 3.0 2, кутова, S28; Molex_Micro-Fit_3.0_43650-0200_1x02_P3.00mm_Horizontal
J315: X29S1-CTRL: JST PH 2, боковий вхід, S29; JST_PH_S2B-PH-K_1x02_P2.00mm_Horizontal
J316: X37S1-CTRL: JST PH 4, боковий вхід, S37; JST_PH_S4B-PH-K_1x04_P2.00mm_Horizontal
J317: X38S1-CTRL: JST PH 4, боковий вхід, S38; JST_PH_S4B-PH-K_1x04_P2.00mm_Horizontal
J318: X39S1-CTRL: JST PH 2, боковий вхід, S39; JST_PH_S2B-PH-K_1x02_P2.00mm_Horizontal
J319: X40S1-CTRL: JST PH 2, боковий вхід, S40; JST_PH_S2B-PH-K_1x02_P2.00mm_Horizontal
Q301, Q302: 2N7002; SOT-23
Q303, Q305: AO3400A; SOT-23
Q304: AO3401A; SOT-23
Q306: 2N7002,215; SOT-23
R301, R302, R305, R306, R307, R308, R309, R310, R311, R312, R313, R314, R315, R316, R317, R318, R319, R320, R321, R322, R323, R324, R325, R328, R330, R334, R351, R352, R353, R354, R355, R356, R357, R358, R368, R392: 10k; R_0603_1608Metric
R326, R329, R331, R366, R367, R371, R394: 100k; R_0603_1608Metric
R327: 200; R_0603_1608Metric
R332, R333: 10k 1%; R_0603_1608Metric
R335, R337, R339, R341, R343, R345, R347, R349, R369: 2.2k; R_0603_1608Metric
R336, R338, R340, R342, R344, R346, R348, R350, R359, R360, R365, R370, R393: 100; R_0603_1608Metric
R361, R362: 4.7k; R_0603_1608Metric
R363: 150; R_0603_1608Metric
R364: 680; R_0603_1608Metric
R395: 1k; R_0603_1608Metric
R396: RILIM TBD (start 162k 1%); R_0603_1608Metric
SW302: HOME momentary NO; SW_E-Switch_TL3145_6.45x6.45mm
SW303: BACK momentary NO; SW_E-Switch_TL3145_6.45x6.45mm
SW304: REC momentary NO; SW_E-Switch_TL3145_6.45x6.45mm
SW305: MARK momentary NO; SW_E-Switch_TL3145_6.45x6.45mm
SW306: FN momentary NO; SW_E-Switch_TL3145_6.45x6.45mm
SW307: LOCK momentary NO; SW_E-Switch_TL3145_6.45x6.45mm
TP301: GNSS 5V switch FAULT_N test point; TestPoint_Pad_D1.5mm
U301: MCP23017-E/SO #1 0x20; SOIC-28W_7.5x17.9mm_P1.27mm
U302: MCP23017-E/SO #3 0x22; SOIC-28W_7.5x17.9mm_P1.27mm
U303: MCP23017-E/SO #4 0x23; SOIC-28W_7.5x17.9mm_P1.27mm
U305: Raspberry Pi Pico SC0915; RaspberryPi_Pico_SMD_SWD
U306: PI4IOE5V9555LEX 0x20; TSSOP-24_4.4x7.8mm_P0.65mm
U307: LM4040C30IDBZR; SOT-23
U310, U311, U312, U313: TPD4E1U06DBVR; SOT-23-6
U315: TPS2553DBVR-1; SOT-23-6

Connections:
3V3_Q6A: C301.1, C302.1, C303.1, C304.1, C305.1, C306.1, J302.1, J304.1, J304.17, J311.2, R301.2, R302.2, R305.2, R306.2, R307.2, R308.2, R309.2, R310.2, R311.2, R312.2, R313.2, R314.2, R315.2, R316.2, R317.2, R318.2, R319.2, R320.2, R321.2, R322.2, R323.2, R324.2, R325.2, R328.1, R392.2, U301.9, U302.9, U302.16, U303.9, U303.15, U303.16, U315.3
CHG_INHIBIT: J306.1, U303.5
DCS_HF: J308.2, R319.1, U302.5
DCS_LBAND: J308.3, R318.1, U302.4
DCS_UHF: J308.4, R317.1, U302.3
E1_BAT_ADC: J306.2, U305.32
E3_ADC3V0: C309.1, R327.2, R332.1, R333.1, U305.35, U307.1
E3_BACK: R337.1, R338.1, U306.5
E3_BACK_EXT: R338.2, SW303.1, U310.3
E3_BEZEL_SCL: J312.2, R360.2, U313.3
E3_BEZEL_SDA: J312.3, R359.2, U313.1
E3_BLOWER_EN: R370.1, U305.25
E3_BLOWER_GATE: Q305.1, R370.2, R371.1
E3_BLOWER_GND: C342.2, C343.2, D306.2, J314.1, Q305.3
E3_BUTTON_SENSE: D302.1, R330.1, U305.15
E3_CASE_TEMP: C311.1, J319.2, R333.2, U305.34
E3_ENC1_A: C314.1, R352.2, U305.4
E3_ENC1_A_RAW: J316.2, R351.1, R352.1, U312.1
E3_ENC1_B: C315.1, R354.2, U305.5
E3_ENC1_B_RAW: J316.3, R353.1, R354.1, U312.3
E3_ENC1_PRESS: R347.1, R348.1, U306.10
E3_ENC1_PRESS_EXT: J316.4, R348.2, U311.4
E3_ENC2_A: C316.1, R356.2, U305.9
E3_ENC2_A_RAW: J317.2, R355.1, R356.1, U312.4
E3_ENC2_B: C317.1, R358.2, U305.10
E3_ENC2_B_RAW: J317.3, R357.1, R358.1, U312.6
E3_ENC2_PRESS: R349.1, R350.1, U306.11
E3_ENC2_PRESS_EXT: J317.4, R350.2, U311.6
E3_FAN5: F301.2, Q304.2
E3_FAN5_P: C318.1, C319.1, D305.1, J313.2, Q304.3
E3_FAN_EN: R365.1, U305.24
E3_FAN_NG: Q303.1, R365.2, R366.1
E3_FAN_PG: Q303.3, Q304.1, R367.1
E3_FAN_TACH: R369.2, U305.29
E3_FAN_TACH_RAW: J313.3, R368.1, R369.1
E3_FN: R343.1, R344.1, U306.8
E3_FN_EXT: R344.2, SW306.1, U311.1
E3_GNSS5V: J311.5, U315.6
E3_GNSS_FAULT: TP301.1, U315.4
E3_GNSS_RESET_GATE: Q301.1, R326.1, U303.22
E3_GNSS_RESET_N: J311.6, Q301.3
E3_HMI_INT: R334.1, U305.14, U306.1
E3_HMI_SCL: R360.1, R362.1, U305.7, U306.22
E3_HMI_SDA: R359.1, R361.1, U305.6, U306.23
E3_HOME: R335.1, R336.1, U306.4
E3_HOME_EXT: R336.2, SW302.1, U310.1
E3_LED_A: D304.A, R364.2
E3_LED_DRIVE: R364.1, U305.27
E3_LOCK: R345.1, R346.1, U306.9
E3_LOCK_EXT: R346.2, SW307.1, U311.3
E3_MARK: R341.1, R342.1, U306.7
E3_MARK_EXT: R342.2, SW305.1, U310.6
E3_MCP_RESET_ASSERT: R393.1, R395.2, U305.22
E3_MCP_RESET_GATE: Q306.1, R393.2, R394.1
E3_MCP_RESET_N: Q306.3, R305.1, R306.1, R307.1, U301.18, U302.18, U303.18
E3_PANEL_TEMP: C310.1, J318.2, R332.2, U305.31
E3_PICO3V3: C308.1, C312.1, C313.1, J312.4, R327.1, R330.2, R334.2, R335.2, R337.2, R339.2, R341.2, R343.2, R345.2, R347.2, R349.2, R351.2, R353.2, R355.2, R357.2, R361.2, R362.2, R368.2, R395.1, U305.36, U306.24
E3_PICO_RUN: J304.38, U305.30
E3_PICO_SWCLK: J304.12, U305.SWCLK
E3_PICO_SWDIO: J304.35, U305.SWDIO
E3_PICO_VSYS: C307.1, D301.1, U305.39
E3_PIEZO_DRIVE: R363.1, U305.26
E3_PIEZO_OUT: BZ301.+, R363.2
E3_Q6A_KEY_GATE: Q302.1, R331.1, U305.16
E3_Q6A_ON_SENSE: R328.2, R329.1, U305.19
E3_REC: R339.1, R340.1, U306.6
E3_REC_EXT: R340.2, SW304.1, U310.4
E3_U315_ILIM: R396.1, U315.5
EN_AUX12: J306.3, U301.22
EN_BONI: J306.4, U301.2
EN_HFP: J306.5, U301.25
EN_LABPORT: J306.6, U301.21
EN_LIME3V3: J306.7, U303.21
EN_LNA1: J306.8, U301.26
EN_LNA2: J306.9, U301.27
EN_LNA3: J306.10, U301.28
EN_LNA4: J306.11, U302.28
EN_LNB: J306.12, U301.1
EN_RTLA: J306.13, U301.23
EN_RTLB: J306.14, U301.24
EN_SB_LNA: J306.15, U303.25
EN_T7: J311.3, U302.8
FAULT_HFP: J306.16, R323.1, U303.2
FAULT_LABPORT: J306.17, R308.1, U302.21
FAULT_LNA1: J306.18, R309.1, U302.22
FAULT_LNA2: J306.19, R310.1, U302.23
FAULT_LNA3: J306.20, R311.1, U302.24
FAULT_LNA4: J307.1, R312.1, U302.25
FAULT_RTLA: J307.2, R324.1, U303.3
FAULT_RTLB: J307.3, R322.1, U303.1
FLT_BONI: J307.4, R314.1, U302.27
FLT_LIME3V3: J307.5, R325.1, U303.4
FLT_LNB: J307.6, R313.1, U302.26
FLT_SB_LNA: J307.7, R392.1, U303.26
GND: BZ301.-, C301.2, C302.2, C303.2, C304.2, C305.2, C306.2, C307.2, C308.2, C309.2, C310.2, C311.2, C312.2, C313.2, C314.2, C315.2, C316.2, C317.2, C318.2, C319.2, C320.2, C321.2, C322.2, D304.K, D305.2, J302.2, J304.9, J304.14, J304.20, J304.25, J304.30, J304.34, J304.39, J305.1, J305.2, J308.1, J310.2, J311.1, J311.4, J312.1, J313.1, J315.1, J316.1, J317.1, J318.1, J319.1, Q301.2, Q302.2, Q303.2, Q305.2, Q306.2, R326.2, R329.2, R331.2, R366.2, R371.2, R394.2, R396.2, SW302.2, SW303.2, SW304.2, SW305.2, SW306.2, SW307.2, U301.10, U301.15, U301.16, U301.17, U302.10, U302.15, U302.17, U303.10, U303.17, U305.3, U305.8, U305.13, U305.18, U305.23, U305.28, U305.33, U305.38, U305.SWD_GND, U306.2, U306.3, U306.12, U306.21, U307.2, U307.3, U310.2, U311.2, U312.2, U313.2, U315.2
I2C0_SCL: J304.15, J307.8
I2C0_SDA: J304.13, J307.9
I2C2_SCL: J302.4, J304.28, U301.12, U302.12, U303.12
I2C2_SDA: J302.3, J304.27, U301.13, U302.13, U303.13
IMU_RX: J307.10, U305.11
IMU_TX: J307.11, U305.12
INA228_ALERT: J304.3, J307.12, R301.1
K1_ON: J308.5, U301.3
K2_ON: J308.6, U301.4
LAB5: C320.1, C321.1, C322.1, C342.1, C343.1, D301.2, D306.1, F301.1, J305.3, J305.4, J314.2, R367.2, U315.1
MCP_INT: J302.5, J304.5, R302.1, U302.19, U302.20, U303.19, U303.20
OVP_LNB_N: J307.13, U303.6
PG_BONI: J307.14, R316.1, U302.2
PG_LNB: J307.15, R315.1, U302.1
PICO_DISP_EN: J307.16, U305.21
PICO_OFF: J307.17, U305.17
PTC_AUX: J307.18, R320.1, U302.6
PWR_BUTTON: D302.3, D303.3, J307.19, J315.2
PWR_ON_KEY: D303.1, J310.1, Q302.3
SAFE_BOOT: J304.40, U305.20
SLED_DET: J307.20, R321.1, U302.7
SW_LIME_A: J308.7, U303.23
SW_LIME_B: J308.8, U303.24
SW_RTLA_A: J309.1, U301.5
SW_RTLA_B: J309.2, U301.6
SW_RTLB_A: J309.3, U301.7
SW_RTLB_B: J309.4, U301.8
UART5_RX: J304.10, J310.3
UART5_TX: J304.8, J310.4
UART7_RX: J304.29, U305.1
UART7_TX: J304.32, U305.2
